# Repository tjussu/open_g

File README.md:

# OpenG Project

__Currently, the project is in the prototyping phase.__

## Overview

The goal of this project is to develop an open-source data logger for soaring and glider aerobatics. The hardware can be built by anyone interested and modified for their own purposes.

## Goals
Specific implementation goals are:

- A watchdog for structural load factors:
    - The load factors are measured in correspondence with the flight envelope (speed & load factors).
    - Critical events will be saved to memory.
    - The load factors can be displayed on a module.
- Path tracing for aerobatics:
    - Tracking of the flight path for training evaluation.
- Easy construction:
    - No difficult-to-solder SMD parts.
    - PCB can be ordered from an online EMS.
    - 3D-printable casing.
    - Construction cost under 450 €.
    - Easy modification.
- Documentation:
    - Hardware documentation.
    - Software documentation.
    - User manual.
    - Technical reference.

We aim to design the hardware in such a way that the system is compliant with EASA regulations. 

## Collaboration
The project is part of a master's thesis conducted at the _Dortmund University of Applied Sciences and Arts_ in cooperation with the _Luftsportfreunde 2000 Kamen/Dortmund club_.

Thanks to both!

## Future Updates
Further information will be provided in the near future.

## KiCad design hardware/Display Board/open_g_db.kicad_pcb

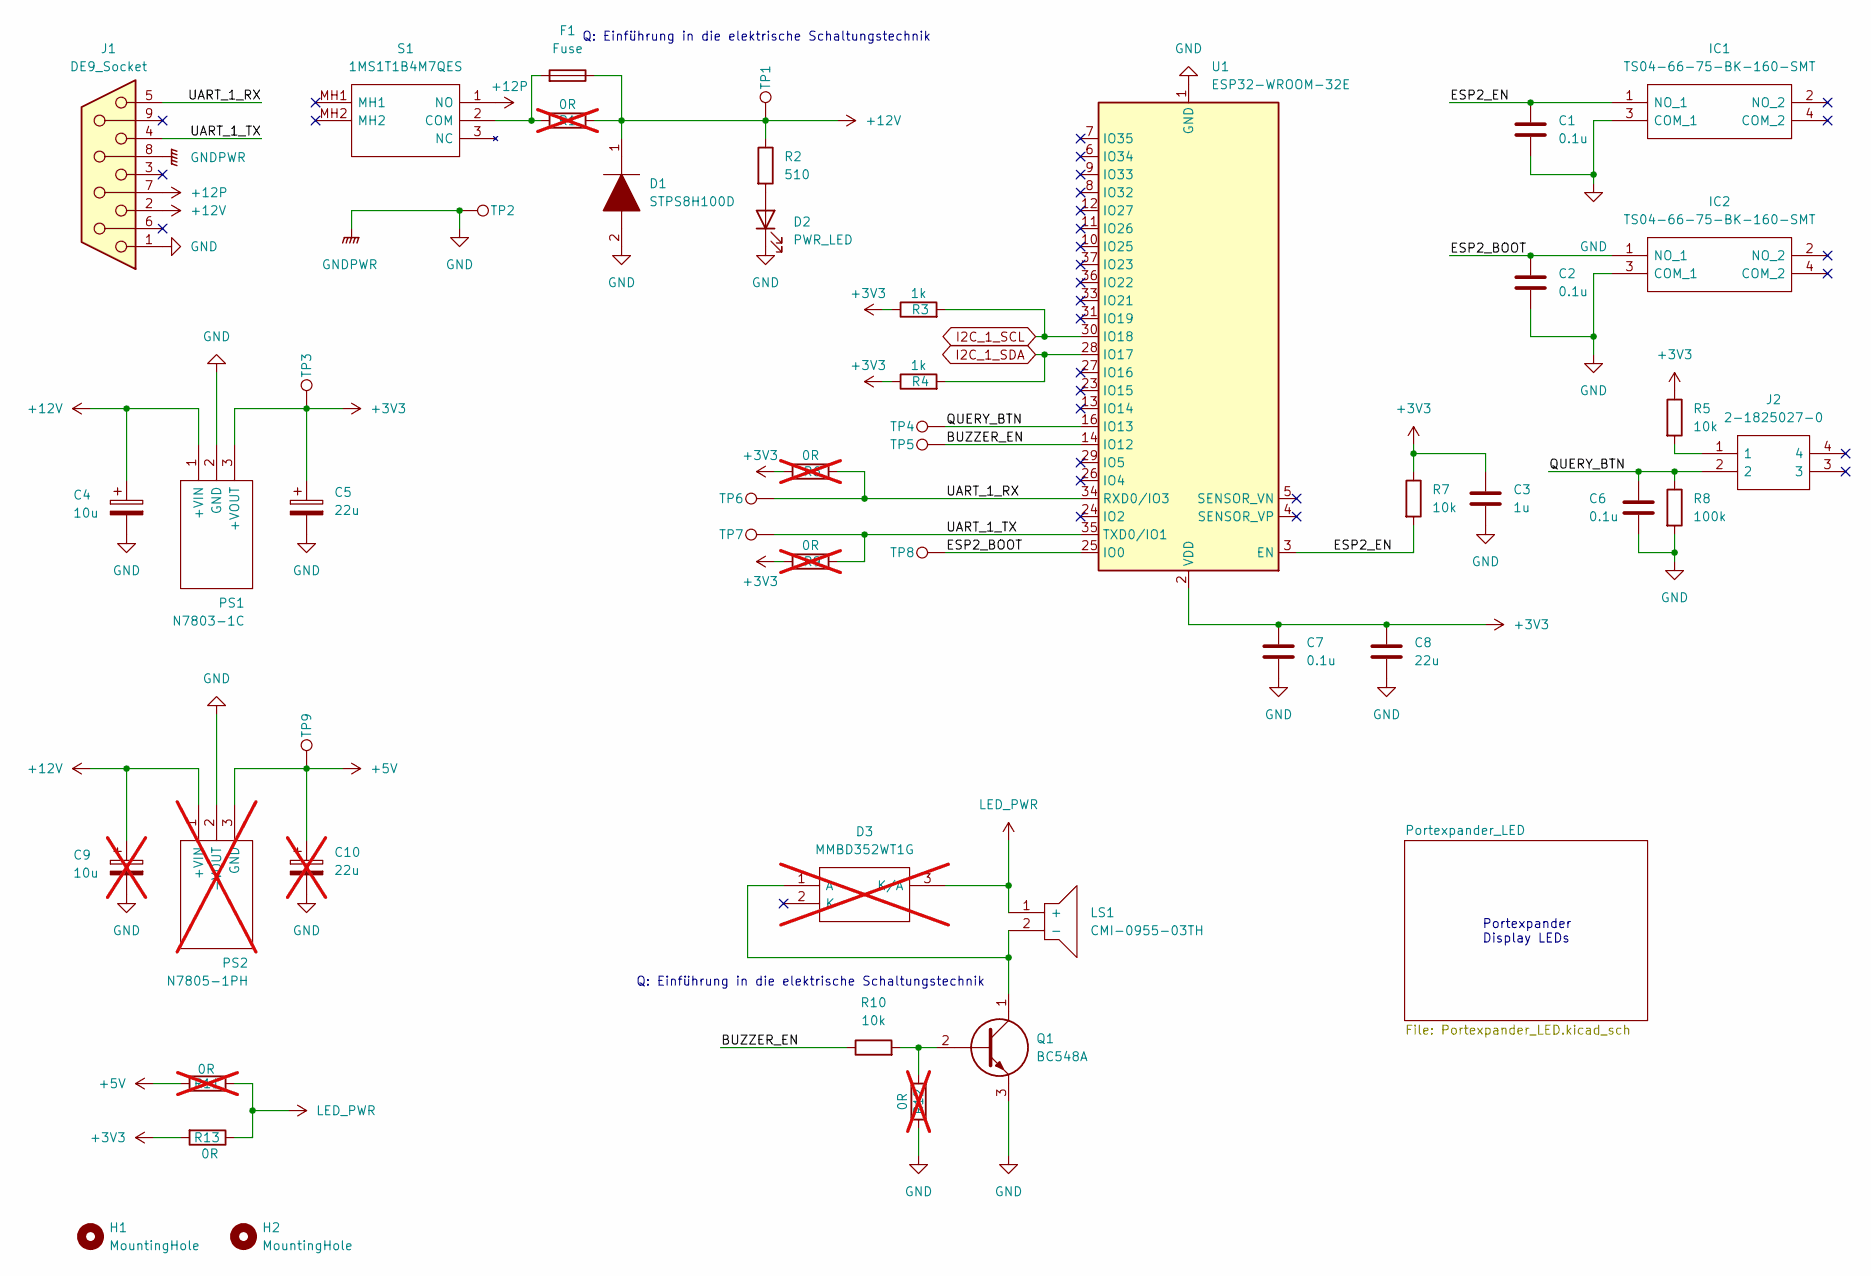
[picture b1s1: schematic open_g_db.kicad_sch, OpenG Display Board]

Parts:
C1, C2, C6, C7: 0.1u; C_0805_2012Metric_Pad1.18x1.45mm_HandSolder
C3: 1u; C_0805_2012Metric_Pad1.18x1.45mm_HandSolder
C4: 10u; CP_Radial_D5.0mm_P2.00mm
C5: 22u; CP_Radial_D5.0mm_P2.00mm
C8: 22u; C_0805_2012Metric_Pad1.18x1.45mm_HandSolder
C9: 10u; CP_Radial_D5.0mm_P2.00mm; not fitted
C10: 22u; CP_Radial_D5.0mm_P2.00mm; not fitted
D1: STPS8H100D; TO515P460X1020X2008-2P; Mouser Part Number 511-STPS8H100D
D2: PWR_LED; LED_D3.0mm_Horizontal_O1.27mm_Z2.0mm_Clear
D3: MMBD352WT1G; SOT65P220X100-3N; Mouser Part Number 863-MMBD352WT1G; not fitted
F1: Fuse; 3557-2
H1, H2: MountingHole; MountingHole_5mm_Pad_Via
IC1, IC2: TS04-66-75-BK-160-SMT; TS046675BK160SMT; Mouser Part Number 179-TS046675BK160SMT
J1: DE9_Socket; NFD17E09SAFC1DA
J2: 2-1825027-0; 218250270; Mouser Part Number 506-2-1825027-0
LS1: CMI-0955-03TH; CMI095503TH; Mouser Part Number 179-CMI-0955-03TH
PS1: N7803-1C; N78031C; Mouser Part Number 709-N7803-1C
PS2: N7805-1PH; N78031C; Mouser Part Number 709-N7805-1PH; not fitted
Q1: BC548A; Mouser Part Number 637-BC548A
R1, R6, R9, R11, R12: 0R; R_0805_2012Metric_Pad1.20x1.40mm_HandSolder; not fitted
R2: 510; R_0805_2012Metric_Pad1.20x1.40mm_HandSolder
R3, R4: 1k; R_0805_2012Metric_Pad1.20x1.40mm_HandSolder
R5, R7, R10: 10k; R_0805_2012Metric_Pad1.20x1.40mm_HandSolder
R8: 100k; R_0805_2012Metric_Pad1.20x1.40mm_HandSolder
R13: 0R; R_0805_2012Metric_Pad1.20x1.40mm_HandSolder
S1: 1MS1T1B4M7QES; Mouser Part Number 118-1MS1T1B4M7QES
TP1, TP2, TP3, TP4, TP5, TP6, TP7, TP8, TP9: TestPoint; TestPoint_Pad_D2.5mm
U1: ESP32-WROOM-32E

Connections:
+3V3: C3.1, C5.1, C7.1, C8.1, PS1.3 (+VOUT), R3.1, R4.1, R5.1, R6.1, R7.1, R9.1, R13.2, TP3.1, U1.2 (VDD); also elsewhere on the board
+5V: C10.1, PS2.3 (GND), R11.2, TP9.1
+12P: J1.7, S1.1 (NO)
+12V: C4.1, C9.1, D1.1, F1.1, J1.2, PS1.1 (+VIN), PS2.1 (+VIN), R1.2, R2.1, TP1.1
/BUZZER_EN: R10.1, TP5.1, U1.14 (IO12)
/ESP2_BOOT: C2.1, IC2.1 (NO_1), TP8.1, U1.25 (IO0)
/ESP2_EN: C1.1, IC1.1 (NO_1), R7.2, U1.3 (EN)
/QUERY_BTN: C6.1, J2.2, R8.1, TP4.1, U1.16 (IO13)
/UART_1_RX: J1.5, R6.2, TP6.1, U1.34 (RXD0/IO3)
/UART_1_TX: J1.4, R9.2, TP7.1, U1.35 (TXD0/IO1)
GND: C1.2, C2.2, C3.2, C4.2, C5.2, C6.2, C7.2, C8.2, C9.2, C10.2, D1.2, D2.1 (K), IC1.3 (COM_1), IC2.3 (COM_1), J1.1, J1.8, PS1.2 (GND), PS2.2 (-VOUT), Q1.3, R8.2, R12.1, TP2.1, U1.1 (GND), U1.15 (GND), U1.38 (GND), U1.39 (GND); also elsewhere on the board
I2C_1_SCL: R3.2, U1.30 (IO18); also elsewhere on the board
I2C_1_SDA: R4.2, U1.28 (IO17); also elsewhere on the board
LED_PWR: D3.3 (K/A), LS1.1 (+), R11.1, R13.1; also elsewhere on the board
unnamed: D2.2 (A), R2.2
unnamed: D3.1 (A), LS1.2 (-), Q1.1
unnamed: J2.1, R5.2
unnamed: Q1.2, R10.2, R12.2
unnamed: F1.2, R1.1, S1.2 (COM)

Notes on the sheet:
Portexpander Display LEDs
Q: Einführung in die elektrische Schaltungstechnik

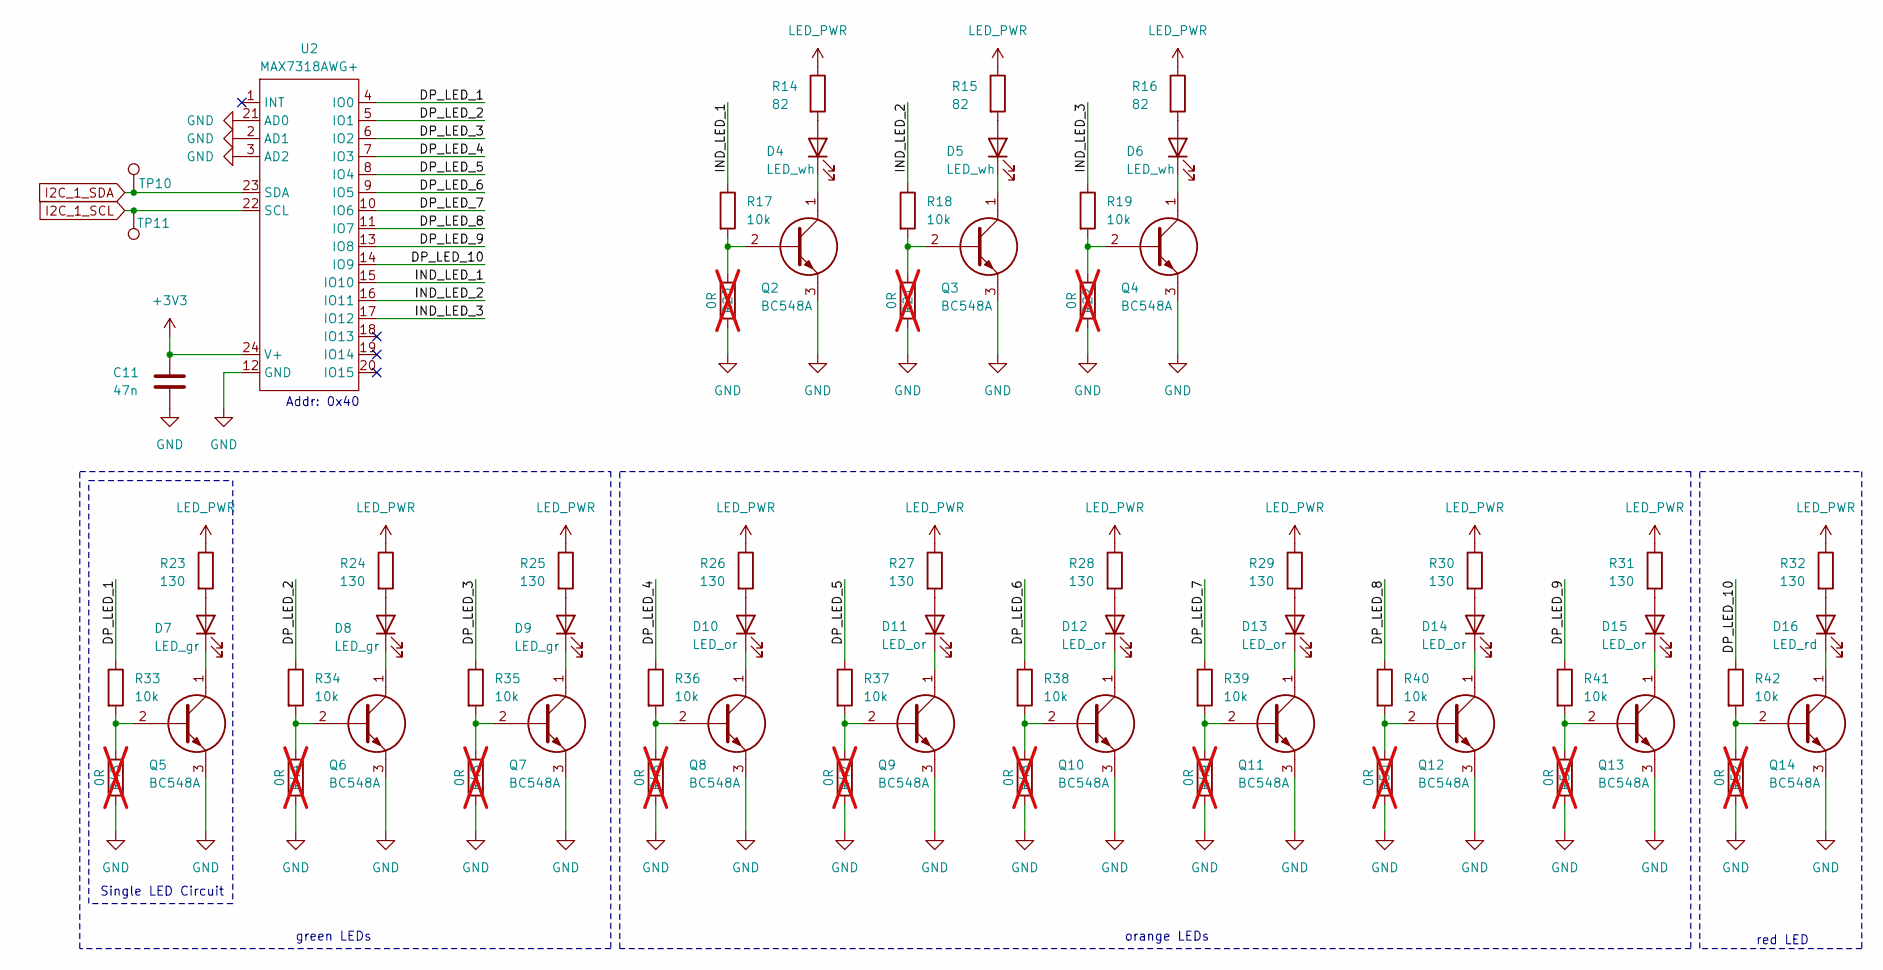
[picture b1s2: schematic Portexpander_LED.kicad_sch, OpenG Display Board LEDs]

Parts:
C11: 47n; C_0805_2012Metric_Pad1.18x1.45mm_HandSolder
D4, D5, D6: LED_wh; LED_D3.0mm_Horizontal_O1.27mm_Z2.0mm_Clear
D7, D8, D9: LED_gr; LED_D3.0mm_Horizontal_O1.27mm_Z2.0mm_Clear
D10, D11, D12, D13, D14, D15: LED_or; LED_D3.0mm_Horizontal_O1.27mm_Z2.0mm_Clear
D16: LED_rd; LED_D3.0mm_Horizontal_O1.27mm_Z2.0mm_Clear
Q2, Q3, Q4, Q5, Q6, Q7, Q8, Q9, Q10, Q11, Q12, Q13, Q14: BC548A; Mouser Part Number 637-BC548A
R14, R15, R16: 82; R_0805_2012Metric_Pad1.20x1.40mm_HandSolder
R17, R18, R19, R33, R34, R35, R36, R37, R38, R39, R40, R41, R42: 10k; R_0805_2012Metric_Pad1.20x1.40mm_HandSolder
R20, R21, R22, R43, R44, R45, R46, R47, R48, R49, R50, R51, R52: 0R; R_0805_2012Metric_Pad1.20x1.40mm_HandSolder; not fitted
R23, R24, R25, R26, R27, R28, R29, R30, R31, R32: 130; R_0805_2012Metric_Pad1.20x1.40mm_HandSolder
TP10, TP11: TestPoint; TestPoint_Pad_D2.5mm
U2: MAX7318AWG+; SOIC-24W_7.5x15.4mm_P1.27mm

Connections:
+3V3: C11.2, U2.24 (V+); also elsewhere on the board
/Portexpander_LED/DP_LED_1: R33.1, U2.4 (IO0)
/Portexpander_LED/DP_LED_2: R34.1, U2.5 (IO1)
/Portexpander_LED/DP_LED_3: R35.1, U2.6 (IO2)
/Portexpander_LED/DP_LED_4: R36.1, U2.7 (IO3)
/Portexpander_LED/DP_LED_5: R37.1, U2.8 (IO4)
/Portexpander_LED/DP_LED_6: R38.1, U2.9 (IO5)
/Portexpander_LED/DP_LED_7: R39.1, U2.10 (IO6)
/Portexpander_LED/DP_LED_8: R40.1, U2.11 (IO7)
/Portexpander_LED/DP_LED_9: R41.1, U2.13 (IO8)
/Portexpander_LED/DP_LED_10: R42.1, U2.14 (IO9)
/Portexpander_LED/IND_LED_1: R17.1, U2.15 (IO10)
/Portexpander_LED/IND_LED_2: R18.1, U2.16 (IO11)
/Portexpander_LED/IND_LED_3: R19.1, U2.17 (IO12)
GND: C11.1, Q2.3, Q3.3, Q4.3, Q5.3, Q6.3, Q7.3, Q8.3, Q9.3, Q10.3, Q11.3, Q12.3, Q13.3, Q14.3, R20.1, R21.1, R22.1, R43.1, R44.1, R45.1, R46.1, R47.1, R48.1, R49.1, R50.1, R51.1, R52.1, U2.2 (AD1), U2.3 (AD2), U2.12 (GND), U2.21 (AD0); also elsewhere on the board
I2C_1_SCL: TP11.1, U2.22 (SCL); also elsewhere on the board
I2C_1_SDA: TP10.1, U2.23 (SDA); also elsewhere on the board
LED_PWR: R14.1, R15.1, R16.1, R23.1, R24.1, R25.1, R26.1, R27.1, R28.1, R29.1, R30.1, R31.1, R32.1; also elsewhere on the board
unnamed: D4.2 (A), R14.2
unnamed: D4.1 (K), Q2.1
unnamed: D5.2 (A), R15.2
unnamed: D5.1 (K), Q3.1
unnamed: D6.2 (A), R16.2
unnamed: D6.1 (K), Q4.1
unnamed: D7.2 (A), R23.2
unnamed: D7.1 (K), Q5.1
unnamed: D8.2 (A), R24.2
unnamed: D8.1 (K), Q6.1
unnamed: D9.2 (A), R25.2
unnamed: D9.1 (K), Q7.1
unnamed: D10.2 (A), R26.2
unnamed: D10.1 (K), Q8.1
unnamed: D11.2 (A), R27.2
unnamed: D11.1 (K), Q9.1
unnamed: D12.2 (A), R28.2
unnamed: D12.1 (K), Q10.1
unnamed: D13.2 (A), R29.2
unnamed: D13.1 (K), Q11.1
unnamed: D14.2 (A), R30.2
unnamed: D14.1 (K), Q12.1
unnamed: D15.2 (A), R31.2
unnamed: D15.1 (K), Q13.1
unnamed: D16.2 (A), R32.2
unnamed: D16.1 (K), Q14.1
unnamed: Q2.2, R17.2, R20.2
unnamed: Q3.2, R18.2, R21.2
unnamed: Q4.2, R19.2, R22.2
unnamed: Q5.2, R33.2, R43.2
unnamed: Q6.2, R34.2, R44.2
unnamed: Q7.2, R35.2, R45.2
unnamed: Q8.2, R36.2, R46.2
unnamed: Q9.2, R37.2, R47.2
unnamed: Q10.2, R38.2, R48.2
unnamed: Q11.2, R39.2, R49.2
unnamed: Q12.2, R40.2, R50.2
unnamed: Q13.2, R41.2, R51.2
unnamed: Q14.2, R42.2, R52.2

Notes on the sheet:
orange LEDs
green LEDs
red LED
Single LED Circuit
Addr: 0x40

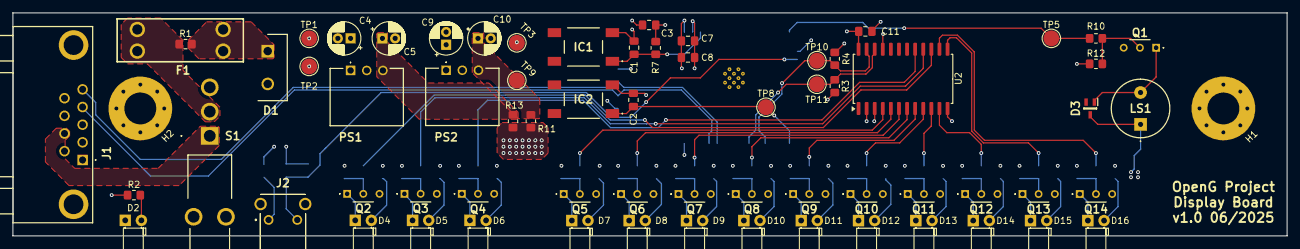
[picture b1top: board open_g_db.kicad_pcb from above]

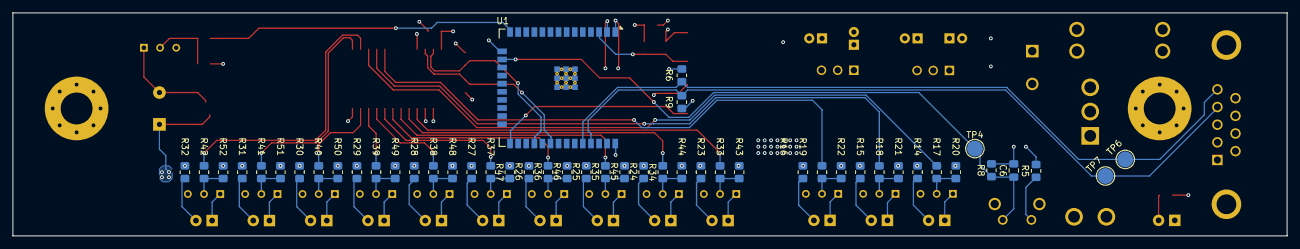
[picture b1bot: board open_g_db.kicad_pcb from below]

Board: 4 copper layers, 200.0 x 35.0 mm, 117 parts (48 on the bottom side), 71 nets.

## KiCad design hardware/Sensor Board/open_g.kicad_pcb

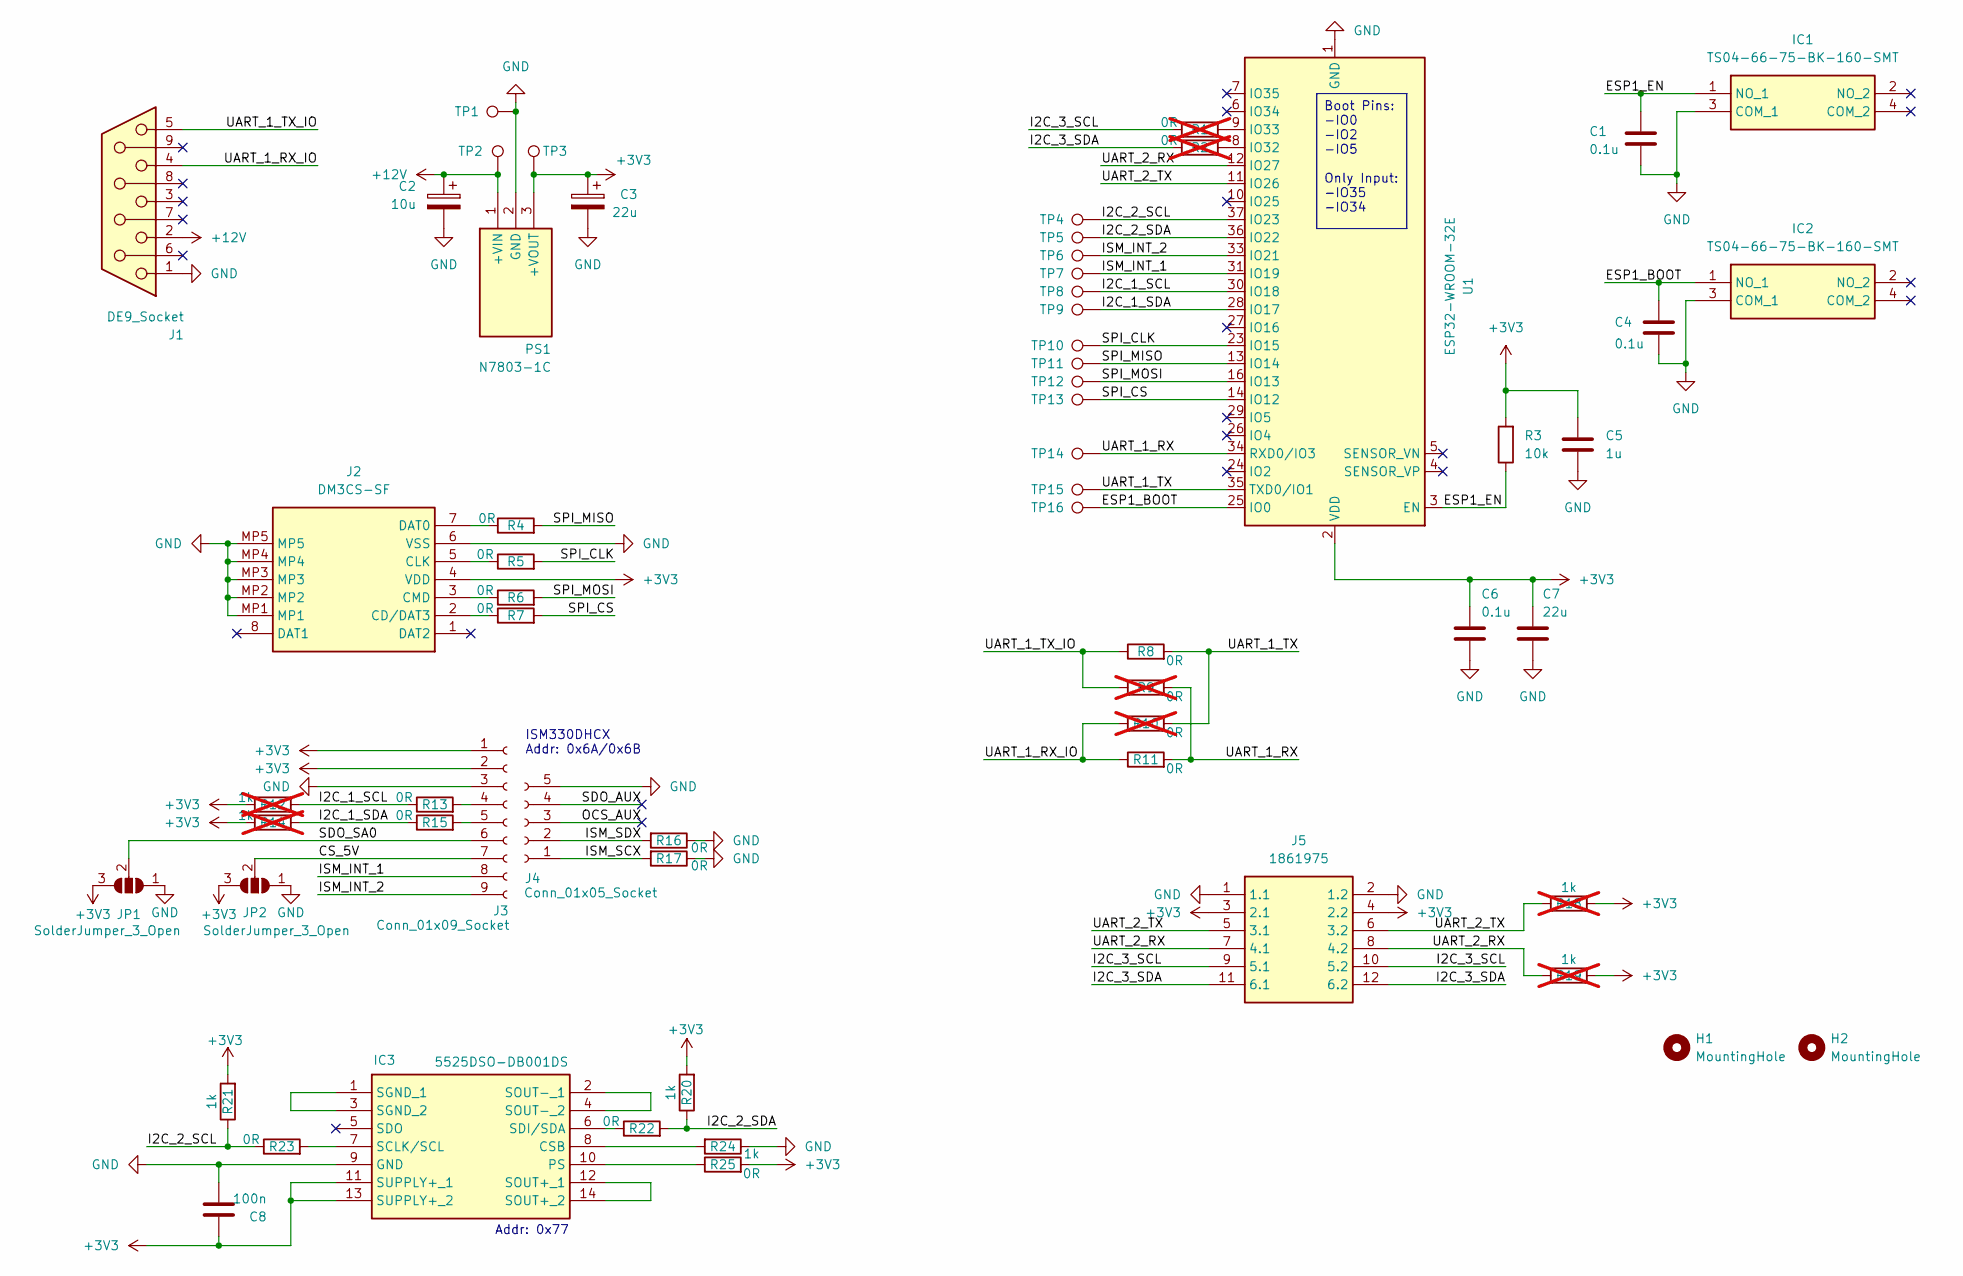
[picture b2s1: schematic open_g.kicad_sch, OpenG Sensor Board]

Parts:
C1, C4, C6: 0.1u; C_0805_2012Metric_Pad1.18x1.45mm_HandSolder
C2: 10u; CP_Radial_D5.0mm_P2.00mm
C3: 22u; CP_Radial_D5.0mm_P2.00mm
C5: 1u; C_0805_2012Metric_Pad1.18x1.45mm_HandSolder
C7: 22u; C_0805_2012Metric_Pad1.18x1.45mm_HandSolder
C8: 100n; C_0805_2012Metric_Pad1.18x1.45mm_HandSolder
H1, H2: MountingHole; MountingHole_5mm_Pad_Via
IC1, IC2: TS04-66-75-BK-160-SMT; TS046675BK160SMT; Mouser Part Number 179-TS046675BK160SMT
IC3: 5525DSO-DB001DS; SOIC-14W_7.5x9mm_P1.27mm; Mouser Part Number 824-5525DSO-DB001DS
J1: DE9_Socket; NFD17E09SAFC1DA
J2: DM3CS-SF; DM3CSSF; Mouser Part Number 798-DM3CSSF
J3: Conn_01x09_Socket; PinSocket_1x09_P2.54mm_Vertical
J4: Conn_01x05_Socket; PinSocket_1x05_P2.54mm_Vertical
J5: 1861975; PC1861975; Mouser Part Number 651-1861975
JP1, JP2: SolderJumper_3_Open; SolderJumper-3_P2.0mm_Open_TrianglePad1.0x1.5mm
PS1: N7803-1C; N78031C; Mouser Part Number 709-N7803-1C
R1, R2, R9, R10: 0R; R_0805_2012Metric_Pad1.20x1.40mm_HandSolder; not fitted
R3: 10k; R_0805_2012Metric_Pad1.20x1.40mm_HandSolder
R4, R5, R6, R7, R8, R11, R13, R15, R16, R17, R22, R23, R25: 0R; R_0805_2012Metric_Pad1.20x1.40mm_HandSolder
R12, R14, R18, R19: 1k; R_0805_2012Metric_Pad1.20x1.40mm_HandSolder; not fitted
R20, R21, R24: 1k; R_0805_2012Metric_Pad1.20x1.40mm_HandSolder
TP1, TP2, TP3, TP4, TP5, TP6, TP7, TP8, TP9, TP10, TP11, TP12, TP13, TP14, TP15, TP16: TestPoint; TestPoint_Pad_D2.5mm
U1: ESP32-WROOM-32E; ESP32-WROOM-32D

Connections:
+3V3: C3.1, C5.1, C6.1, C7.1, C8.1, IC3.11 (SUPPLY+_1), IC3.13 (SUPPLY+_2), J2.4 (VDD), J3.1, J3.2, J5.3 (2.1), J5.4 (2.2), JP1.3 (B), JP2.3 (B), PS1.3 (+VOUT), R3.2, R12.2, R14.2, R18.2, R19.2, R20.2, R21.2, R25.2, TP3.1, U1.2 (VDD)
+12V: C2.1, J1.2, PS1.1 (+VIN), TP2.1
/CS_5V: J3.7, JP2.2 (C)
/ESP1_BOOT: C4.1, IC2.1 (NO_1), TP16.1, U1.25 (IO0)
/ESP1_EN: C1.1, IC1.1 (NO_1), R3.1, U1.3 (EN)
/I2C_1_SCL: R12.1, R13.1, TP8.1, U1.30 (IO18)
/I2C_1_SDA: R14.1, R15.1, TP9.1, U1.28 (IO17)
/I2C_2_SCL: R21.1, R23.1, TP4.1, U1.37 (IO23)
/I2C_2_SDA: R20.1, R22.2, TP5.1, U1.36 (IO22)
/I2C_3_SCL: J5.9 (5.1), J5.10 (5.2), R1.1
/I2C_3_SDA: J5.11 (6.1), J5.12 (6.2), R2.1
/ISM_INT_1: J3.8, TP7.1, U1.31 (IO19)
/ISM_INT_2: J3.9, TP6.1, U1.33 (IO21)
/ISM_SCX: J4.1, R17.2
/ISM_SDX: J4.2, R16.2
/OCS_AUX: J4.3
/SDO_AUX: J4.4
/SDO_SA0: J3.6, JP1.2 (C)
/SPI_CLK: R5.2, TP10.1, U1.23 (IO15)
/SPI_CS: R7.2, TP13.1, U1.14 (IO12)
/SPI_MISO: R4.2, TP11.1, U1.13 (IO14)
/SPI_MOSI: R6.2, TP12.1, U1.16 (IO13)
/UART_1_RX: R9.2, R11.2, TP14.1, U1.34 (RXD0/IO3)
/UART_1_RX_IO: J1.4, R10.1, R11.1
/UART_1_TX: R8.2, R10.2, TP15.1, U1.35 (TXD0/IO1)
/UART_1_TX_IO: J1.5, R8.1, R9.1
/UART_2_RX: J5.7 (4.1), J5.8 (4.2), R19.1, U1.12 (IO27)
/UART_2_TX: J5.5 (3.1), J5.6 (3.2), R18.1, U1.11 (IO26)
GND: C1.2, C2.2, C3.2, C4.2, C5.2, C6.2, C7.2, C8.2, IC1.3 (COM_1), IC2.3 (COM_1), IC3.9 (GND), J1.1, J2.6 (VSS), J2.MP1, J2.MP2, J2.MP3, J2.MP4, J2.MP5, J3.3, J4.5, J5.1 (1.1), J5.2 (1.2), JP1.1 (A), JP2.1 (A), PS1.2 (GND), R16.1, R17.1, R24.1, TP1.1, U1.1 (GND), U1.15 (GND), U1.38 (GND), U1.39 (GND)
unnamed: IC3.8 (CSB), R24.2
unnamed: IC3.10 (PS), R25.1
unnamed: IC3.7 (SCLK/SCL), R23.2
unnamed: IC3.6 (SDI/SDA), R22.1
unnamed: IC3.1 (SGND_1), IC3.3 (SGND_2)
unnamed: IC3.12 (SOUT+_1), IC3.14 (SOUT+_2)
unnamed: IC3.2 (SOUT-_1), IC3.4 (SOUT-_2)
unnamed: J2.2 (CD/DAT3), R7.1
unnamed: J2.5 (CLK), R5.1
unnamed: J2.3 (CMD), R6.1
unnamed: J2.7 (DAT0), R4.1
unnamed: J3.4, R13.2
unnamed: J3.5, R15.2
unnamed: R2.2, U1.8 (IO32)
unnamed: R1.2, U1.9 (IO33)

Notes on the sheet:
Addr: 0x77
ISM330DHCX Addr: 0x6A/0x6B
Boot Pins: -IO0 -IO2 -IO5 Only Input: -IO35 -IO34

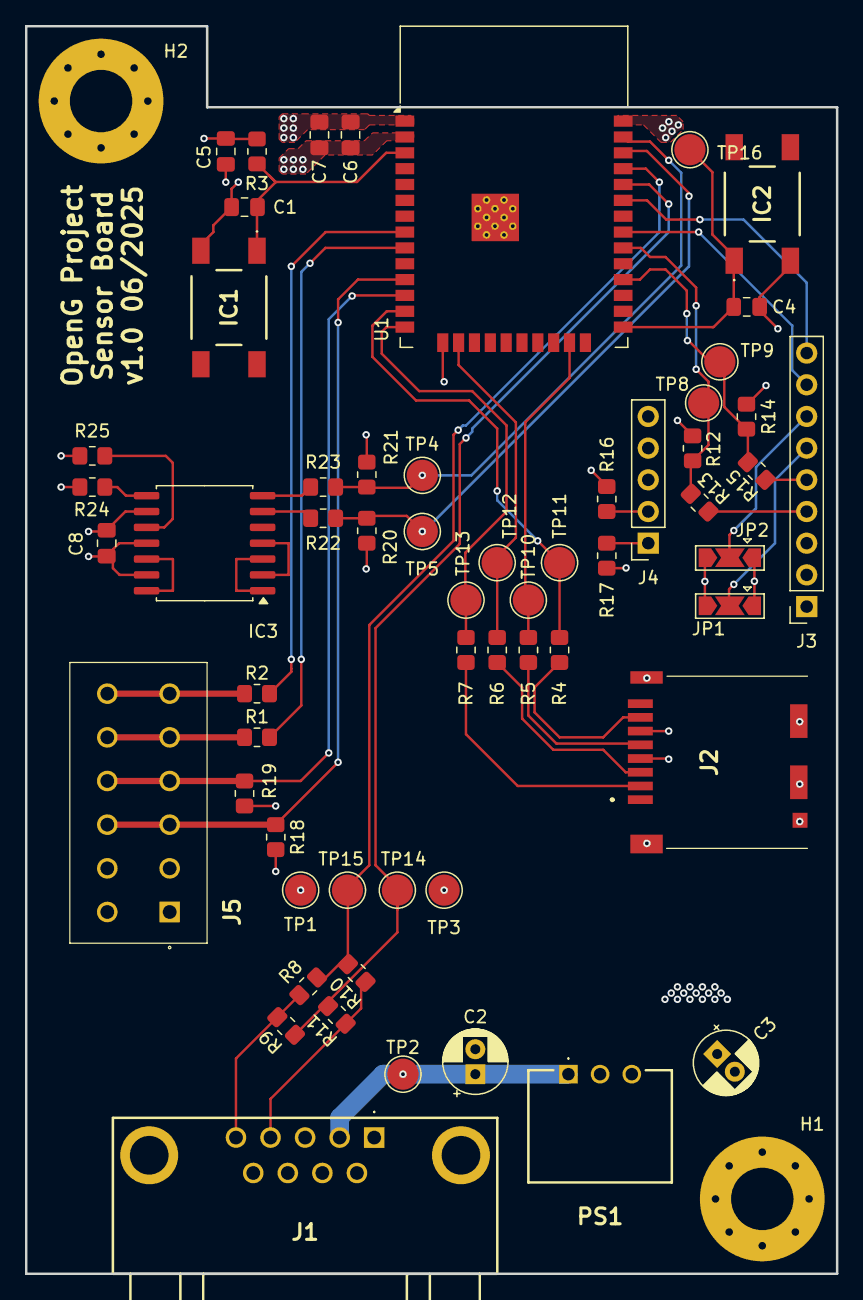
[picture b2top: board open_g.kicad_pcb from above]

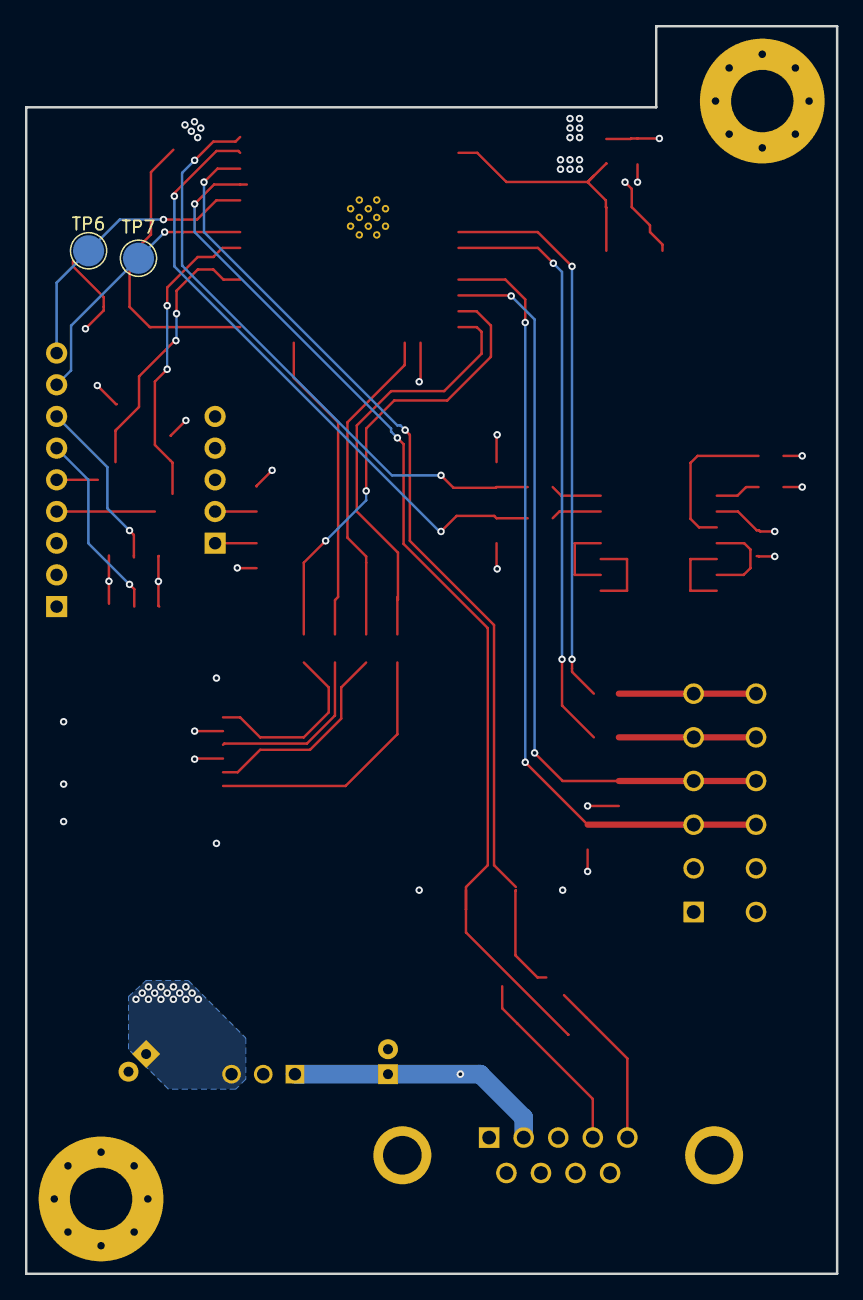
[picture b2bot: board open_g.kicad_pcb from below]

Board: 4 copper layers, 65.0 x 100.0 mm, 63 parts (2 on the bottom side), 42 nets.

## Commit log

2024-11-29 added docs folder and gitignore
2024-11-29 updated requirements
2024-11-29 style changes to requirements
2024-12-05 added requirements
2025-01-03 added new requirements (mostly functional)
2025-06-17 added v1.0 schematics, layouts, gerbers, libs and other files
2025-06-18 added README and minor changes
2025-07-21 added gerbers and initial for firmware; changed README

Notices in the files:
hardware/Display Board/Portexpander_LED.kicad_sch:
License: GNU GPLv3
